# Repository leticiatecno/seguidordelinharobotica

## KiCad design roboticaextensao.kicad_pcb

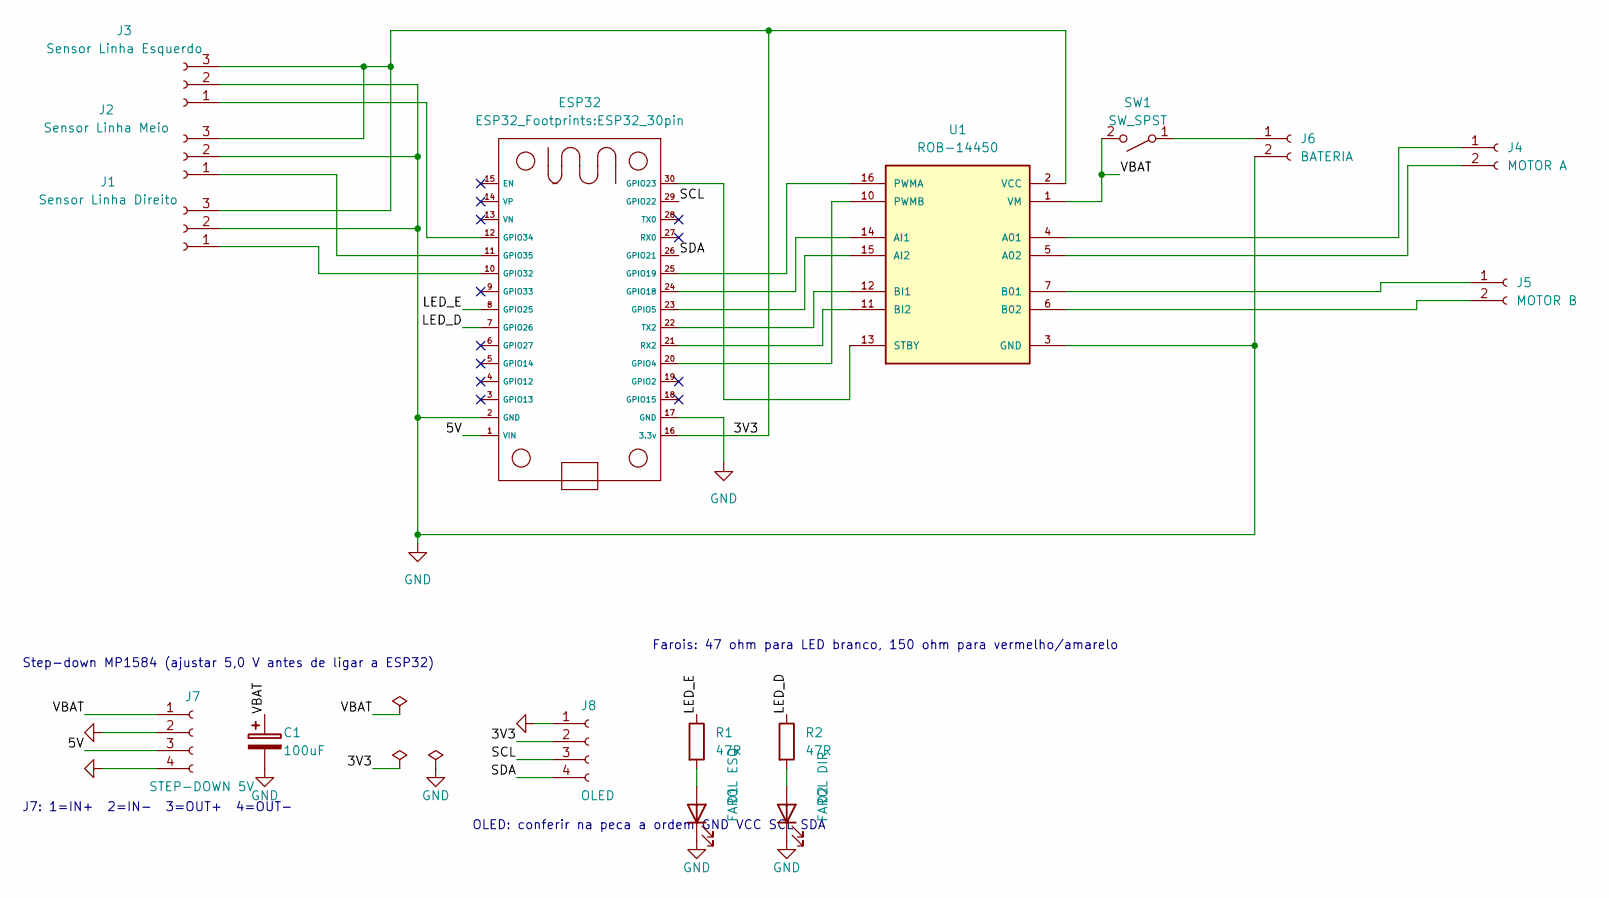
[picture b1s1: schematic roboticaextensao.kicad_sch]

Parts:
C1: 100uF; CP_Radial_D6.3mm_P2.50mm
D1: FAROL ESQ; LED_D5.0mm
D2: FAROL DIR; LED_D5.0mm
ESP32: ESP32_30pin
J1: Sensor Linha Direito; PinSocket_1x03_P2.54mm_Horizontal
J2: Sensor Linha Meio; PinSocket_1x03_P2.54mm_Horizontal
J3: Sensor Linha Esquerdo; PinSocket_1x03_P2.54mm_Horizontal
J4: MOTOR A; TerminalBlock_Phoenix_MKDS-1,5-2-5.08_1x02_P5.08mm_Horizont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
J5: MOTOR B; TerminalBlock_Phoenix_MKDS-1,5-2-5.08_1x02_P5.08mm_Horizont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
J6: BATERIA; TerminalBlock_Phoenix_MKDS-1,5-2-5.08_1x02_P5.08mm_Horizont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
J7: STEP-DOWN 5V; PinSocket_1x04_P2.54mm_Vertical
J8: OLED; PinSocket_1x04_P2.54mm_Vertical
R1, R2: 47R; R_Axial_DIN0207_L6.3mm_D2.5mm_P10.16mm_Horizontal
SW1: SW_SPST; TerminalBlock_Phoenix_MKDS-1,5-2-5.08_1x02_P5.08mm_Horizont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
U1: ROB-14450; MODULE_ROB-14450; PARTREV 11-13-17

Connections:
/3V3: ESP32.16 (3.3v), J1.3, J2.3, J3.3, J8.2, U1.2 (VCC)
/5V: ESP32.1 (VIN), J7.3
/LED_D: ESP32.7 (GPIO26), R2.1
/LED_E: ESP32.8 (GPIO25), R1.1
/SCL: ESP32.29 (GPIO22), J8.3
/SDA: ESP32.26 (GPIO21), J8.4
/VBAT: C1.1, J7.1, SW1.2 (B), U1.1 (VM)
GND: C1.2, D1.1 (K), D2.1 (K), ESP32.2 (GND), ESP32.17 (GND), J1.2, J2.2, J3.2, J6.2, J7.2, J7.4, J8.1, U1.3 (GND), U1.8 (GND), U1.9 (GND)
unnamed: D1.2 (A), R1.2
unnamed: D2.2 (A), R2.2
unnamed: ESP32.20 (GPIO4), U1.10 (PWMB)
unnamed: ESP32.23 (GPIO5), U1.15 (AI2)
unnamed: ESP32.24 (GPIO18), U1.14 (AI1)
unnamed: ESP32.25 (GPIO19), U1.16 (PWMA)
unnamed: ESP32.30 (GPIO23), U1.13 (STBY)
unnamed: ESP32.10 (GPIO32), J1.1
unnamed: ESP32.12 (GPIO34), J3.1
unnamed: ESP32.11 (GPIO35), J2.1
unnamed: ESP32.21 (RX2), U1.11 (BI2)
unnamed: ESP32.22 (TX2), U1.12 (BI1)
unnamed: J4.1, U1.4 (A01)
unnamed: J4.2, U1.5 (A02)
unnamed: J5.1, U1.7 (B01)
unnamed: J5.2, U1.6 (B02)
unnamed: J6.1, SW1.1 (A)

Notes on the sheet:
OLED: conferir na peca a ordem GND VCC SCL SDA
Farois: 47 ohm para LED branco, 150 ohm para vermelho/amarelo
Step-down MP1584 (ajustar 5,0 V antes de ligar a ESP32)
J7: 1=IN+ 2=IN- 3=OUT+ 4=OUT-

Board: 2 copper layers, 16 parts (0 on the bottom side), 25 nets, no tracks yet.
